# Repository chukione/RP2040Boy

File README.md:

# ~~Arduino~~RP2040boy
~~Official~~ ArduinoBoy port to RP2040 uC, its cheapear than a avr uC, it have so much more ram than a avr. The available boards come with megabytes of flash space, making ideal to use a oled display instead of the leds array.

On the breadboard photo, im using a transistor and a led, but is removed on the schematic because is a non sense. In original code (what i left untouched), the optoisolator is powered without condition on setup() 

USB midi with TynyUSB lib, and serial midi work.

At the moment, the only tested mode is mGB. LSJD midiout via usb is broken (serial must work, but its disabled.)

I normaly use linux, the dependencies and the pico toolchain is installed automacally on vscode with platformio extension, but on windows, you need to enable long paths on both git, and windows as described [here](https://arduino-pico.readthedocs.io/en/latest/platformio.html#important-steps-for-windows-users-before-installing). On arduino ide, you need to add the Earle Philhower core as described [here](https://learn.adafruit.com/rp2040-arduino-with-the-earlephilhower-core/installing-the-earlephilhower-core), also need to add the u8g2 library and the forty seven effects midi library and select the tinyusb usb stack on the menu.

Repository for serial MIDI communication to the Nintendo Gameboy.

## About 
Arduinoboy is software for the [Arduino hardware platform](http://arduino.cc) that allows serial communication (MIDI) to the Nintendo Gameboy for music applications such as [LittleSoundDJ](http://littlesounddj.com), [Nanoloop.](http://www.nanoloop.com/), and [mGB](https://github.com/trash80/mGB)

## Current Features
* Affordable and easily accessible parts for assembly.
* Accurate MIDI Sync, Start and Stop commands.
* Push Button selector sets the sync/state modes [(7 modes available)](#modes-details)
* [mGB](https://github.com/trash80/mGB)
 Mode: Full MIDI in support across all Gameboy Channels, including a unique "poly" mode allows you to play your Game Boy like a synthesizer. 
* Midi Out Doubles as a Midi Thru
* "Filtering" data for only sync messages, no dedicated MIDI line required.
* Can be powered by the Game Boy's gamelink port.
* USB upgradeable via Arduino.
* Midi settings configurable using a Mac/PC editor built in Max.
* Tested and works with DMG (Original), Gameboy Color, and Advance/SP.

## Modes Details
#### Mode 1 - LSDJ as MIDI Slave Sync
Slave your Game Boy running [LittleSoundDJ](http://littlesounddj.com) to your midi sequencer or Digital audio workstation.  

You can send the arduinoboy midi notes to change sync resolution and start/stop the LSDJ sequencer.  

_LSDJ Slave Mode Midi Note Effects:_

* 48 - `C-2` Sends a Sequencer Start Command
* 49 - `C#2` Sends a Sequencer Stop Command
* 50 - `D-2` Toggles Normal Tempo 
* 51 - `D#2` Toggles 1/2 Tempo
* 52 - `E-2` Toggles 1/4 Tempo
* 53 - `F-2` Toggles 1/8 Tempo

Higher note values than these map LSDJ song position row offset on a Song Start.

In LSDJ the `sync` mode should be set to `Slave`
 
#### Mode 2 LSDJ as MIDI Master Sync. 

Send Midi sync with LSDJ as a midi clock master, LSDJ also sends a Midi Note on message that corresponds to the song row number on play.

In LSDJ the `sync` mode should be set to `Master`

#### Mode 3 LSDJ PC Keyboard mode.
This mode emulates the [PC Keyboard Mode](http://littlesounddj.wikia.com/wiki/PC_Keyboard_Interface) built into LSDJ, allowing you to control the following aspects of LSDJ: 

Features:

* The first octave controls M-U-T-E, 
* Cursor control (LSDJ Live mode only), 
* Table selection
* Table cue.

_PC Keyboard mode midi note map_

* 36 - `C-1` Mute Pu1 Off/On
* 37 - `C#1` Mute Pu2 Off/On
* 38 - `D-1` Mute Wav Off/On
* 39 - `D#1` Mute Noi Off/On
* 40 - `E-1` Livemode Cue Sequence
* 41 - `F-1` Livemode Cursor Up
* 42 - `F#1` Livemode Cursor Down
* 43 - `G-1` Livemode Cursor Left
* 44 - `G#1` Live mode Cursor Right
* 45 - `A-1` Table Up
* 46 - `A#1` Table Down
* 47 - `B-1` Cue Table
* 48+ - Notes from this note up will accept midi in from an external keyboard or sequencer and allow you to play the notes`C-2 to C-8`.  
* Midi Program Change messages will select from instrument table
* Default Midi channel is 16. You can set this in the top of the main source file in the archive, or via the [Max Pat editor](#max).

In LSDJ the `sync` mode should be set to `Keyboard`

#### Mode 4 MIDI to Nanoloop sync
Sync [Nanoloop.](http://www.nanoloop.com/) to external midi clock signals sent to the midi in.

In Nanoloop, the sync mode should be set to `slave`.

#### Mode 5 Full MIDI with mGB
[mGB](https://github.com/trash80/mGB) is a Gameboy cartridge program (You need a Flash Cart and Transfer hardware) That enables the Gameboy to act as a MIDI supported sound module that allows full control of the Game Boy sound hardware. 

It works with the old DMG Gameboy as well as GBC/GBA.

#### Mode 6 LSDJ MIDIMAP 
Lsdj will sync to incoming MIDI sync, and incoming MIDI notes are mapped to LSDJ's song row #. The currently selected row's MIDI note is displayed on the top right of the LSDJ screen, and incoming MIDI notes will also display the relative song row number in the same location.

In LSDJ the `sync` mode should be set to `MI.MAP`. 

*This requires a special version of LSDJ, which can be found in your account on the [LSDJ website](http://littlesounddj.com/lsd/latest/full_version/).*

#### Mode 7 LSDJ MIDIOUT
Each of the 4 gameboy channels send MIDI data on 4 midi channels by the use of effects commands:

* `Nxx` - Sends a MIDI Note - Absolute to the value placed in the effect. N00 sends note off, `N01`-`N6F` send midi notes 1 to 112.
* `Qxx` - Sends a [MIDI Note](http://www.electronics.dit.ie/staff/tscarff/Music_technology/midi/midi_note_numbers_for_octaves.htm) relative to the current channel's pitch. The effect value is a offset. so `Q0C` in `PU1` would send a note 1 octave higher than what `PU1` is currently playing. This is useful as a table command to track midi notes as normal notes in the sequencer.
* `Xxx` - Sends a MIDI CC - By default in Arduinoboy the high nibble selects a CC#, and the low nibble sends a value `0-F` to `0-127`. This can be changed to allow just 1 midi CC with a range of `00`-`6F`, or 7 CCs with scaled or unscaled values.
* `Yxx` - Sends a program/patch/preset change.

By default each channel of LSDJ is mapped to midi channels 1-4. For example note commands from PU1 will be sent to midi channel 1. 

In LSDJ the `sync` mode should be set to `Midiout`. 

*This requires a special version of LSDJ, which can be found in your account on the [LSDJ website](http://littlesounddj.com/lsd/latest/full_version/).*

## Max Editor

[The Arduinoboy Editor for Max](https://github.com/trash80/Arduinoboy/tree/master/Editor) for PC/OSX machines is a gui editor that allows you to edit the various global midi settings of your arduinoboy without editing or flashing code, over midi. It used to required the now deprecated Max Runtime, but you can also run it using a demo of [Cycling '74's Max application](https://cycling74.com/downloads/)

### Maxpat Settings
* `Midi In/Out`
Connect your arduinoboy to these ports on your system. Once it has connected, all the lights on your arduinoboy should flash in order, and the editor will show a green `Connected`.
* `Mode` 
Setting this will tell your arduinoboy what mode to boot into automatically. This is handy if you built your own arduinoboy and decided you wanted to skimp out on LEDs and a button.
* `LSDJ Slave Mode settings` - The midi channel LSDJ slave mode will receive its commands on.
* `LSDJ Master Mode settings` - The midi channel LSDJ Master mode will send its midi notes mapped to row number on.
* `Keyboard Mode settings` - What channel LSDJ will look for its keyboard mode midi commands. No idea what compatibility mode does.
* `mGB midi settings` - Map each incoming midi channel to a specific Gameboy channel in mGB.
* `LSDJ Livesync/Livemap settings` - The midi channel Livesync/Livemap will listen to incoming midi commands from.
* `LSDJ Midiout settings` - Here you can set the following:
	* `Note midi channel` -  The channel each LSDJ channel will send it's midi note commands on.
	* `CC midi channel` -  The channel each LSDJ channel will send it's Continuous Controller commands on.
	* `CC 0` - The initial CC each channel will send. The type of data it will send is based on the next setting.
	* `CC Mode` - Game Boys have limitations! You can either have arduinoboy send one CC with many values, or 7 with limited 8bit values. By default in Arduinoboy the high nibble selects a CC#, and the low nibble sends a value [0-F] to [0-127]. This can be changed to allow just 1 midi CC with a range of 00-6F, or 7 CCs with scaled or unscaled values.
	* `CC Scaling ` - Set wether the 7 CCs are scaled or unscaled.

## Future Features & wishlist
  * Build instructions, and a Arduino Shield

## How To build an Arduinoboy

* [Build Photos](http://flickr.com/photos/trash80/2316803175/in/set-72157604068871573/)
* [Old version (Pre 1.1.0)](http://trash80.net/junkfood/arduinoboy/arduinoboy-schem-v.0.9.8-r1.png)

### Video Demos

  * [Keyboard Mode Test](http://youtube.com/watch?v=TnLUuvc78XY)
  * [Sync Demos](http://youtube.com/watch?v=iVmhy-Lo7BI)
  * [Arduino inside of Gameboy DMG](http://youtube.com/watch?v=VwrMuOA0VnY)
  * [mGB Example & Arduinoboy build into a DMG](http://vimeo.com/1853931)
  * [PDF explores mGB with a MIDI guitar](http://www.youtube.com/watch?v=HAU9MzZ2qeE)

## Thanks To
  * [Arduino](http://arduino.cc)
  * [Nitro2k01](http://blog.gg8.se/wordpress/) for ASM help with mGB 
  * [GWEM](http://www.preromanbritain.com/gwem/lsdj_midi/g33k.html) g33k page
  * [Midines](http://wayfar.net) Thanks for the help x|k!
  * [firestARTer](http://www.firestarter-music.de) help with keyboard & Midi handling information. 
  * [Gijs Gieskes](http://gieskes.nl) Found source code that gave insight into Nanoloop sync
  * [Little Sound DJ](http://littlesounddj.com)
  * [http://devrs.com/gb](http://devrs.com/gb) Madcatz PC link port for gb serial specs
  * [http://chipmusic.org](http://chipmusic.org) For all things Chipmusic.

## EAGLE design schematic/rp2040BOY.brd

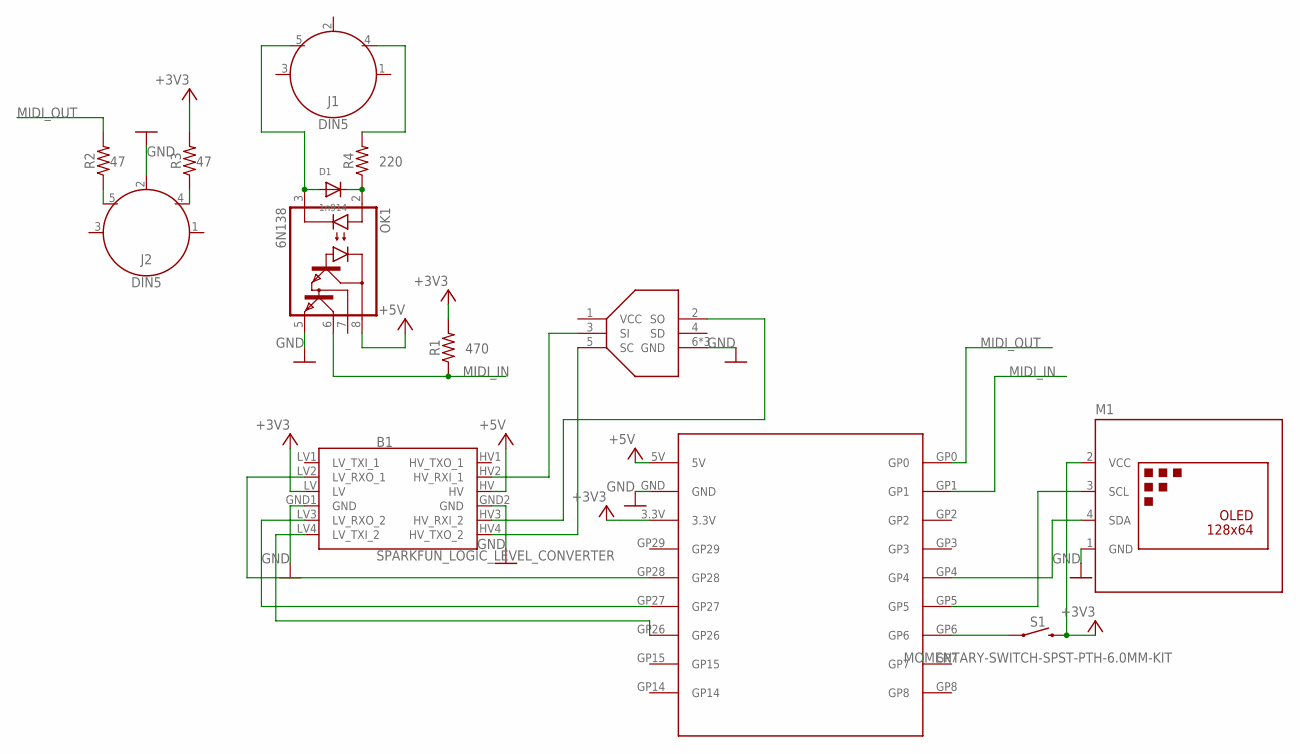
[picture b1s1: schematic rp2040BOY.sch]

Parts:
B1: SPARKFUN_LOGIC_LEVEL_CONVERTER
D1: 1n914; DO-1N4148
J1, J2: DIN5; DIN5-RA-PTH
M1: OLED-128X64-I2C-NH; DISPLAY-OLED-128X64-I2C_NH
OK1: 6N138; DIL08
R1: 470; AXIAL-0.3
R2, R3: 47; AXIAL-0.3
R4: 220; AXIAL-0.3
S1: MOMENTARY-SWITCH-SPST-PTH-6.0MM-KIT; TACTILE_SWITCH_PTH_6.0MM_KIT
U$1: GBC_LINK_CONN; GBC
U$2: RP2040-ZERO-ROUND; RP2040-ZERO_O

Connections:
+3V3: B1.LV, M1.2 (VCC), R1.P$2 (2), R3.P$2 (2), S1.3 (2), U$2.3.3V
+5V: B1.HV, OK1.8 (VCC), U$2.5V
GND: B1.GND1 (GND), B1.GND2 (GND), J2.2, M1.1 (GND), OK1.5 (GND), U$1.6 (GND), U$1.P$7 (GND), U$1.P$8 (GND), U$2.GND
MIDI_IN: OK1.6 (VO), R1.P$1 (1), U$2.GP1
MIDI_OUT: R2.P$2 (2), U$2.GP0
unnamed: B1.LV4 (LV_TXI_2), U$2.GP26
unnamed: B1.LV3 (LV_RXO_2), U$2.GP27
unnamed: B1.LV2 (LV_RXO_1), U$2.GP28
unnamed: B1.HV3 (HV_RXI_2), U$1.2 (SO)
unnamed: B1.HV2 (HV_RXI_1), U$1.3 (SI)
unnamed: B1.HV4 (HV_TXO_2), U$1.5 (SC)
unnamed: S1.1, U$2.GP6
unnamed: M1.4 (SDA), U$2.GP4
unnamed: M1.3 (SCL), U$2.GP5
unnamed: D1.A, J1.5, OK1.3 (C)
unnamed: D1.C, OK1.2 (A), R4.P$1 (1)
unnamed: J2.5, R2.P$1 (1)
unnamed: J2.4, R3.P$1 (1)
unnamed: J1.4, R4.P$2 (2)

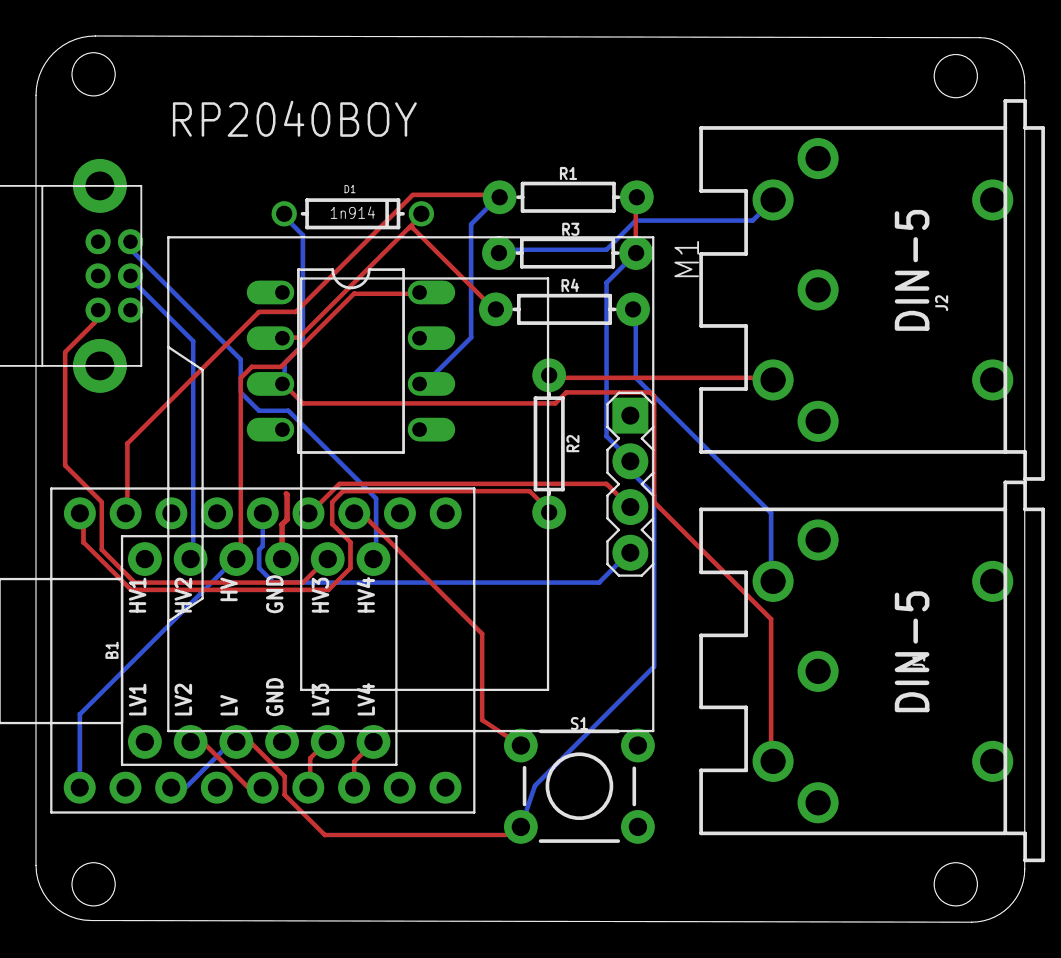
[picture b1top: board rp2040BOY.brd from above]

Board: 2 copper layers, 54.9 x 49.2 mm, 13 parts (0 on the bottom side), 19 nets.

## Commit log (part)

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2024-07-05 LSDJ midiout broken (commented)
2024-07-05 indented
2024-07-06 readme edited
2024-07-12 mGB serial midi tested
2024-07-12 schematic updated
2024-07-13 added serial midi oled display, and usb or serial icons
2024-07-13 readme updated.
2024-07-13 removed old schematic without serial midi
2024-08-02 fixed miditype cast on lsdj midiout
2024-08-11 eagle files added
2024-08-29 windows build notes added to readme
2024-08-29 typo
2024-10-07 Actualizar README.md
    typos
2024-10-07 Actualizar README.md
    more typos
2026-02-24 mode 6 fix

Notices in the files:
parts and their libraries:
SparkFun-Boards: Licensing: Creative Commons ShareAlike 4.0 International - https://creativecommons.org/licenses/by-sa/4.0
